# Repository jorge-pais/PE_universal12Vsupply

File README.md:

# Power Electronics - Final Project

This project is a simple and efficient universal 12V switch mode power supply circuit, designed and built for the final project of the Power Electronics Course at KU Leuven - Group T. It is designed around Texas Instruments' LM5175 buck-boost controller IC in order to provide currents up to 2A with an input voltage ranging from 4V to 24V.

## Circuit and PCB

Both the schematic capture and PCB design were done utilizing KiCad 7. These project files can be found the `universal12Vsupply` folder.

It is possible to preview the project online without KiCad through [KiCanvas](https://kicanvas.org/?github=https%3A%2F%2Fgithub.com%2Fjorge-pais%2FPE_universal12Vsupply%2Ftree%2Fmain%2Funiversal12Vsupply).

#### Front View

#### Back View

## Credits

This project was the collaborative effort of the following team members:

- Jorge Pais
- Ranlin Huang
- Samriddha Ray

Their hard work and dedication made this project a success.

## License

This project is licensed under the [Open Source Hardware License 2](LICENSE.md)

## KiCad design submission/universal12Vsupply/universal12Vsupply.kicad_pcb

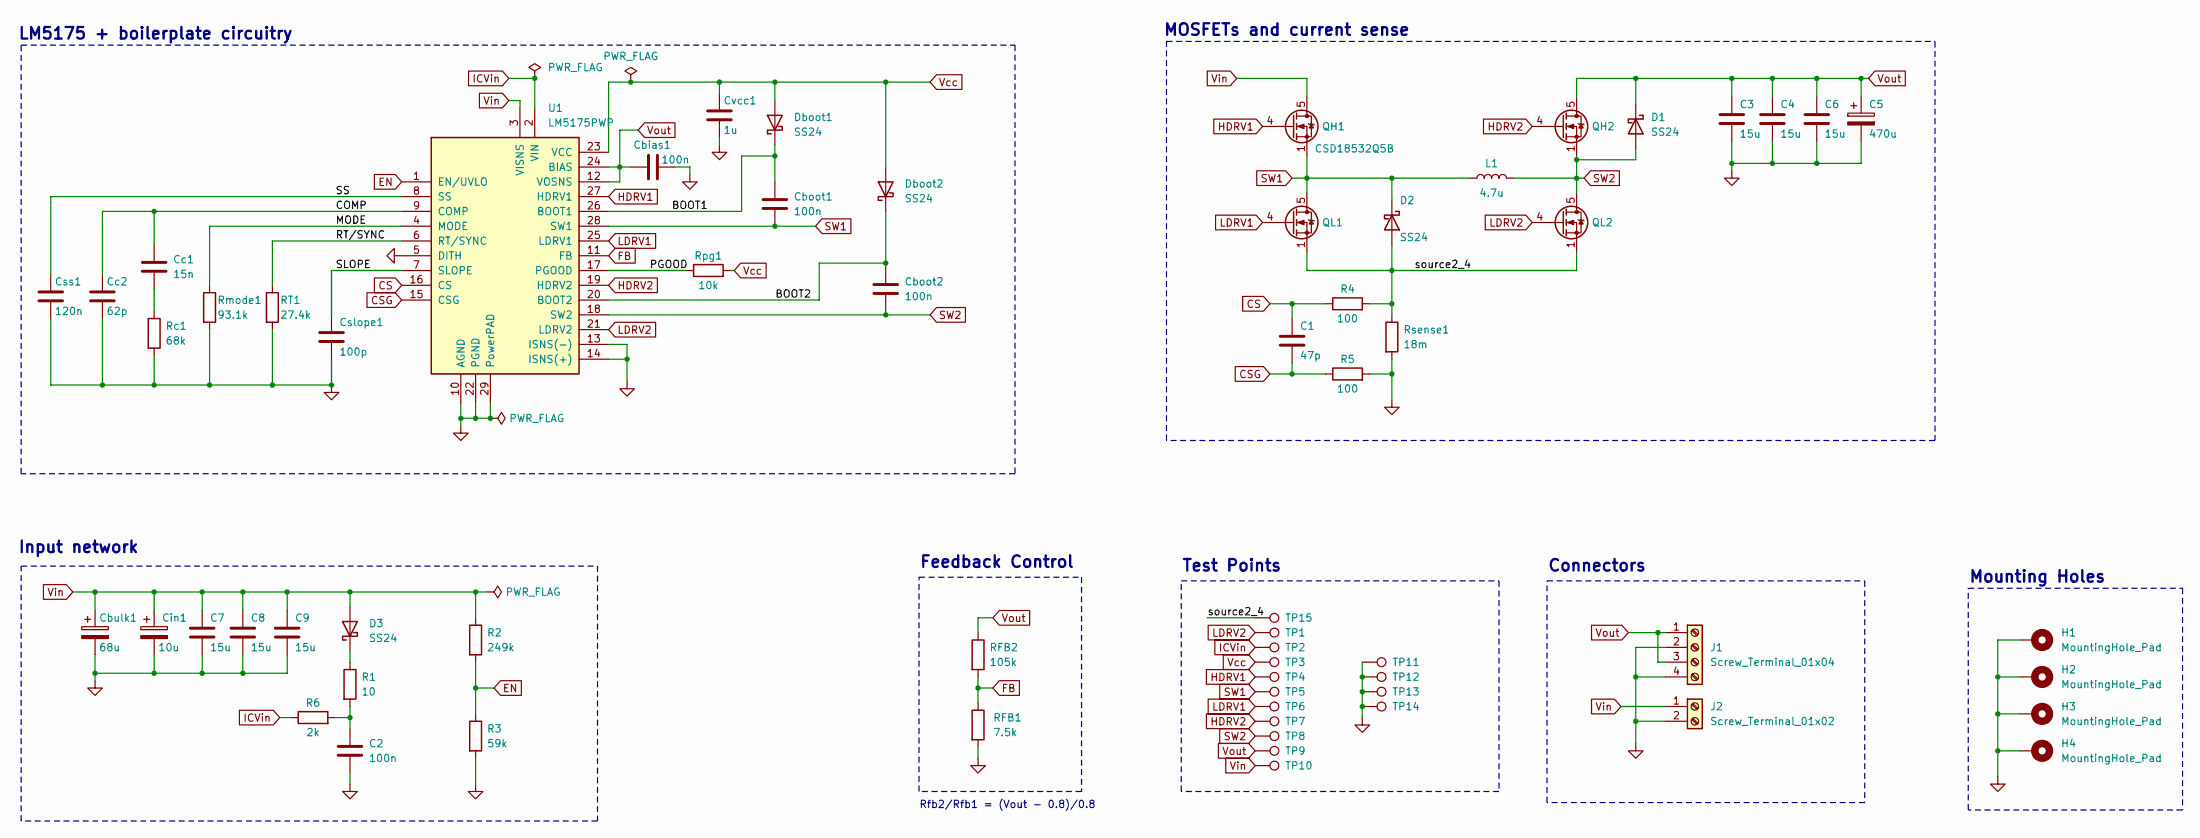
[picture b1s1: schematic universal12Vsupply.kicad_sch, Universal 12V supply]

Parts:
C1: 47p; C_0603_1608Metric_Pad1.08x0.95mm_HandSolder
C2: 100n; C_0805_2012Metric_Pad1.18x1.45mm_HandSolder
C3, C4, C6, C7, C8, C9: 15u; C_1206_3216Metric_Pad1.33x1.80mm_HandSolder
C5: 470u; CP_Elec_10x12.6
Cbias1: 100n; C_0805_2012Metric_Pad1.18x1.45mm_HandSolder
Cboot1, Cboot2: 100n; C_0805_2012Metric_Pad1.18x1.45mm_HandSolder
Cbulk1: 68u; CP_Elec_10x10.5
Cc1: 15n; C_0603_1608Metric_Pad1.08x0.95mm_HandSolder
Cc2: 62p; C_0603_1608Metric_Pad1.08x0.95mm_HandSolder
Cin1: 10u; CP_Elec_5x5.4
Cslope1: 100p; C_0603_1608Metric_Pad1.08x0.95mm_HandSolder
Css1: 120n; C_0603_1608Metric_Pad1.08x0.95mm_HandSolder
Cvcc1: 1u; C_0603_1608Metric_Pad1.08x0.95mm_HandSolder
D1, D2, D3: SS24; D_SMB_Handsoldering
Dboot1, Dboot2: SS24; D_SMB_Handsoldering
H1, H2, H3, H4: MountingHole_Pad; MountingHole_3.2mm_M3_Pad_Via
J1: Screw_Terminal_01x04; TerminalBlock_bornier-4_P5.08mm
J2: Screw_Terminal_01x02; TerminalBlock_bornier-2_P5.08mm
L1: 4.7u; L_Coilcraft_XAL1010-XXX_handsolder
QH1, QH2: CSD18532Q5B; TDSON-8-1
QL1, QL2: CSD18532Q5B; TDSON-8-1
R1: 10; R_0603_1608Metric_Pad0.98x0.95mm_HandSolder
R2: 249k; R_0603_1608Metric_Pad0.98x0.95mm_HandSolder
R3: 59k; R_0603_1608Metric_Pad0.98x0.95mm_HandSolder
R4, R5: 100; R_0603_1608Metric_Pad0.98x0.95mm_HandSolder
R6: 2k; R_0603_1608Metric_Pad0.98x0.95mm_HandSolder
RFB1: 7.5k; R_0603_1608Metric_Pad0.98x0.95mm_HandSolder
RFB2: 105k; R_0603_1608Metric_Pad0.98x0.95mm_HandSolder
RT1: 27.4k; R_0603_1608Metric_Pad0.98x0.95mm_HandSolder
Rc1: 68k; R_0603_1608Metric_Pad0.98x0.95mm_HandSolder
Rmode1: 93.1k; R_0603_1608Metric_Pad0.98x0.95mm_HandSolder
Rpg1: 10k; R_0603_1608Metric_Pad0.98x0.95mm_HandSolder
Rsense1: 18m; R_2512_6332Metric_Pad1.40x3.35mm_HandSolder
TP1: LDRV2; TestPoint_THTPad_2.5x2.5mm_Drill1.2mm
TP2: ICVin; TestPoint_THTPad_2.5x2.5mm_Drill1.2mm
TP3: Vcc; TestPoint_THTPad_2.5x2.5mm_Drill1.2mm
TP4: HDRV1; TestPoint_THTPad_2.5x2.5mm_Drill1.2mm
TP5: SW1; TestPoint_THTPad_2.5x2.5mm_Drill1.2mm
TP6: LDRV1; TestPoint_THTPad_2.5x2.5mm_Drill1.2mm
TP7: HDRV2; TestPoint_THTPad_2.5x2.5mm_Drill1.2mm
TP8: SW2; TestPoint_THTPad_2.5x2.5mm_Drill1.2mm
TP9: Vout; TestPoint_THTPad_2.5x2.5mm_Drill1.2mm
TP10: Vin; TestPoint_THTPad_2.5x2.5mm_Drill1.2mm
TP11, TP12, TP13, TP14: gnd; TestPoint_THTPad_2.5x2.5mm_Drill1.2mm
TP15: source2_4; TestPoint_THTPad_2.5x2.5mm_Drill1.2mm
U1: LM5175PWP; HTSSOP-28-1EP_4.4x9.7mm_P0.65mm_EP3.4x9.5mm_ThermalVias

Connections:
/BOOT1: Cboot1.1, Dboot1.1 (K), U1.26 (BOOT1)
/BOOT2: Cboot2.1, Dboot2.1 (K), U1.20 (BOOT2)
/COMP: Cc1.1, Cc2.1, U1.9 (COMP)
/MODE: Rmode1.1, U1.4 (MODE)
/PGOOD: Rpg1.1, U1.17 (PGOOD)
/RT/SYNC: RT1.1, U1.6 (RT/SYNC)
/SLOPE: Cslope1.1, U1.7 (SLOPE)
/SS: Css1.1, U1.8 (SS)
/source2_4: D2.2 (A), QL1.1 (S), QL1.2 (S), QL1.3 (S), QL2.1 (S), QL2.2 (S), QL2.3 (S), R4.2, Rsense1.1, TP15.1
CS: C1.1, R4.1, U1.16 (CS)
CSG: C1.2, R5.1, U1.15 (CSG)
EN: R2.2, R3.1, U1.1 (EN/UVLO)
FB: RFB1.1, RFB2.2, U1.11 (FB)
GND: C2.2, C3.2, C4.2, C5.2, C6.2, C7.2, C8.2, C9.2, Cbias1.2, Cbulk1.2, Cc2.2, Cin1.2, Cslope1.2, Css1.2, Cvcc1.2, H1.1, H2.1, H3.1, H4.1, J1.2, J1.4, J2.2, R3.2, R5.2, RFB1.2, RT1.2, Rc1.2, Rmode1.2, Rsense1.2, TP11.1, TP12.1, TP13.1, TP14.1, U1.5 (DITH), U1.10 (AGND), U1.13 (ISNS(-)), U1.14 (ISNS(+)), U1.22 (PGND), U1.29 (PowerPAD)
HDRV1: QH1.4 (G), TP4.1, U1.27 (HDRV1)
HDRV2: QH2.4 (G), TP7.1, U1.19 (HDRV2)
ICVin: R6.1, TP2.1, U1.2 (VIN)
LDRV1: QL1.4 (G), TP6.1, U1.25 (LDRV1)
LDRV2: QL2.4 (G), TP1.1, U1.21 (LDRV2)
unnamed: C2.1, R1.2, R6.2
unnamed: Cc1.2, Rc1.1
unnamed: D3.1 (K), R1.1
SW1: Cboot1.2, D2.1 (K), L1.1, QH1.1 (S), QH1.2 (S), QH1.3 (S), QL1.5 (D), TP5.1, U1.28 (SW1)
SW2: Cboot2.2, D1.2 (A), L1.2, QH2.1 (S), QH2.2 (S), QH2.3 (S), QL2.5 (D), TP8.1, U1.18 (SW2)
Vcc: Cvcc1.1, Dboot1.2 (A), Dboot2.2 (A), Rpg1.2, TP3.1, U1.23 (VCC)
Vin: C7.1, C8.1, C9.1, Cbulk1.1, Cin1.1, D3.2 (A), J2.1, QH1.5 (D), R2.1, TP10.1, U1.3 (VISNS)
Vout: C3.1, C4.1, C5.1, C6.1, Cbias1.1, D1.1 (K), J1.1, J1.3, QH2.5 (D), RFB2.1, TP9.1, U1.12 (VOSNS), U1.24 (BIAS)

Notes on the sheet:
Feedback Control
MOSFETs and current sense
Rfb2/Rfb1 = (Vout - 0.8)/0.8
Mounting Holes
Input network
Connectors
LM5175 + boilerplate circuitry
Test Points

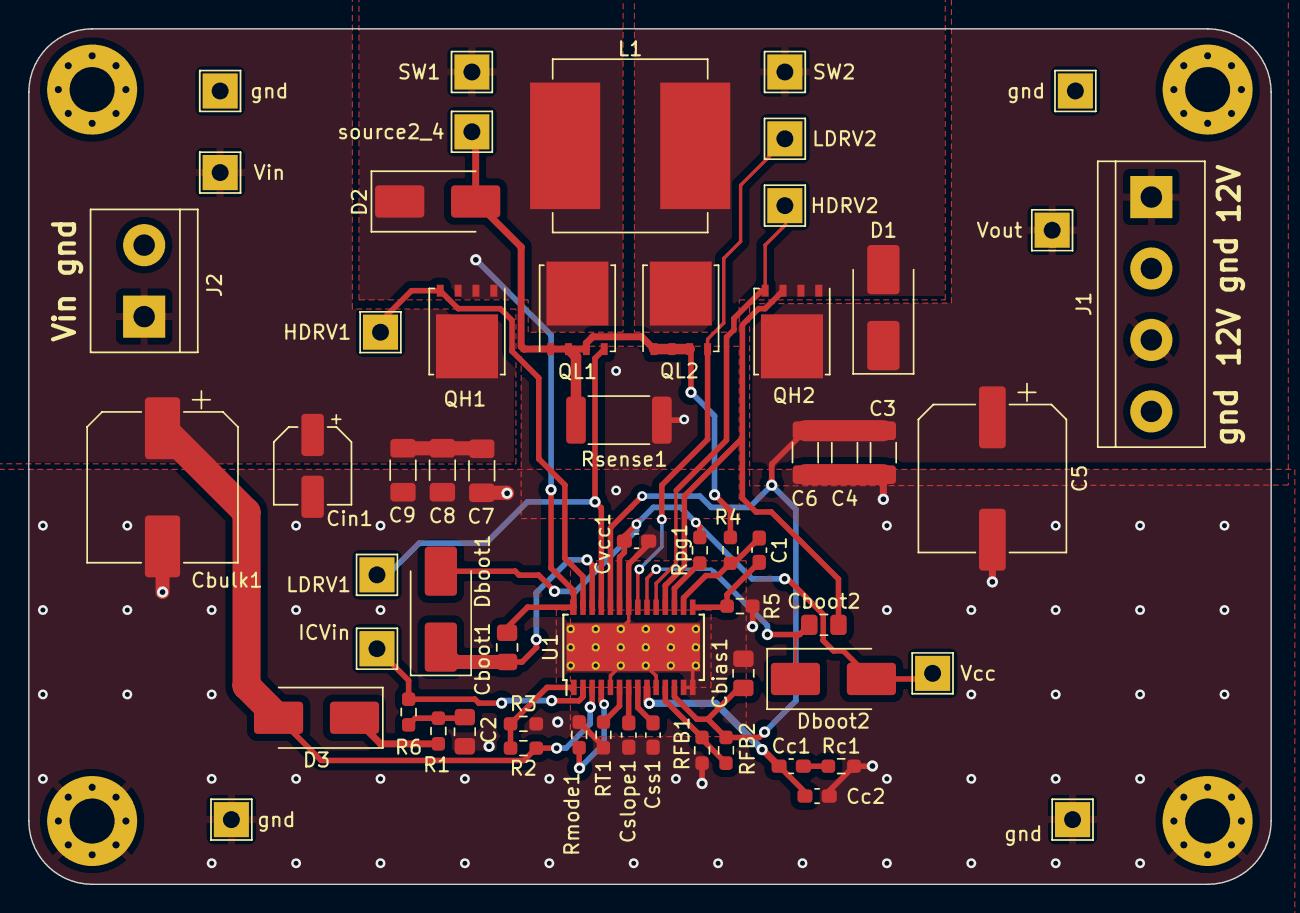
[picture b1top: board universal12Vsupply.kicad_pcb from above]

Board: 2 copper layers, 88.3 x 60.8 mm, 64 parts (0 on the bottom side), 27 nets.

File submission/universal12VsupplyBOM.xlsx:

Reference | Value | Footprint | Datasheet | Farnell | Qty | Order Code
C1 | 47p | Capacitor_SMD:C_0603_1608Metric_Pad1.08x0.95mm_HandSolder | ~ | https://be.farnell.com/en-BE/kemet/c0603c470f1gactu/cap-47pf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 | 1 | 2820807
C2 | 100n | Capacitor_SMD:C_0805_2012Metric_Pad1.18x1.45mm_HandSolder | ~ | https://be.farnell.com/en-BE/kemet/c0805x104j5rac3316/cap-0-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 | 1 | 2666904
C3, C4, C6, C7, C8, C9 | 15u | Capacitor_SMD:C_1206_3216Metric_Pad1.33x1.80mm_HandSolder | ~ | https://be.farnell.com/en-BE/avx/tpsa156k006r0700/cap-15-f-6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 | 6 | 1658485
C5 | 470u | Capacitor_SMD:CP_Elec_10x12.6 | ~ | https://be.farnell.com/en-BE/panasonic/25svpk470m/cap-470-f-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 | 1 | 2759084
Cbias1 | 100n | Capacitor_SMD:C_0805_2012Metric_Pad1.18x1.45mm_HandSolder | ~ | https://be.farnell.com/en-BE/kemet/c0805x104j5rac3316/cap-0-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 | 1 | 2666904
Cboot1, Cboot2 | 100n | Capacitor_SMD:C_0805_2012Metric_Pad1.18x1.45mm_HandSolder | ~ | https://be.farnell.com/en-BE/kemet/c0805x104j5rac3316/cap-0-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 | 2 | 2666904
Cbulk1 | 68u | Capacitor_SMD:CP_Elec_10x10.5 | ~ | https://be.farnell.com/en-BE/panasonic/eehzt1j680p/cap-68uf-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 | 1 | 3584428
Cc1 | 15n | Capacitor_SMD:C_0603_1608Metric_Pad1.08x0.95mm_HandSolder | ~ | https://be.farnell.com/en-BE/multicomp/mc0603b153j500ct/cap-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 | 1 | 2320805
Cc2 | 62p | Capacitor_SMD:C_0603_1608Metric_Pad1.08x0.95mm_HandSolder | ~ | https://be.farnell.com/en-BE/kemet/c0603c620j5gactu/cap-62pf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 | 1 | 1865482
Cin1 | 10u | Capacitor_SMD:CP_Elec_5x5.4 | ~ | https://be.farnell.com/en-BE/kemet/exv106m035a9daa/cap-10-f-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 | 1 | 2069187
Cslope1 | 100p | Capacitor_SMD:C_0603_1608Metric_Pad1.08x0.95mm_HandSolder | ~ | https://be.farnell.com/en-BE/kemet/c0603x101f5gacauto/cap-10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 | 1 | 2904893
Cvcc1 | 1u | Capacitor |  | https://be.farnell.com/en-BE/kemet/c0805c105j8ractu/cap-1-f-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 | 1 | 2773210
Css1 | 120n | Capacitor_SMD:C_0603_1608Metric_Pad1.08x0.95mm_HandSolder | ~ | https://be.farnell.com/en-BE/kemet/c0603c124k8ractu/cap-0-12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 | 1 | 2821085
D1-D3 | SS24 | Diode_SMD:D_SMB_Handsoldering | ~ | https://be.farnell.com/en-BE/multicomp/ss24/schottky-rectifi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 | 3 | 2675138
Dboot1, Dboot2 | SS24 | Diode_SMD:D_SMB_Handsoldering | ~ | https://be.farnell.com/en-BE/multicomp/ss24/schottky-rectifi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 | 2 | 2675138
L1 | 4.7u | Inductor_SMD:L_Coilcraft_XAL1010-XXX | ~ | https://be.farnell.com/en-BE/coilcraft/xal1010-472med/induct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 | 1 | 2289017
QH1, QH2 | CSD18532Q5B | Package_TO_SOT_SMD:TDSON-8-1 | http://www.ti.com/lit/gpn/csd18532q5b | https://be.farnell.com/en-BE/texas-instruments/csd18532q5b/m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 | 2 | 3009663
QL1, QL2 | CSD18532Q5B | Package_TO_SOT_SMD:TDSON-8-1 | http://www.ti.com/lit/gpn/csd18532q5b | https://be.farnell.com/en-BE/texas-instruments/csd18532q5b/m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 | 2 | 3009663
R1 | 10R | Resistor_SMD:R_0603_1608Metric_Pad0.98x0.95mm_HandSolder | ~ | https://be.farnell.com/en-BE/rohm/ktr03ezpf10r0/res-10r-1-0-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 | 1 | 2919225
R2 | 249k | Resistor_SMD:R_0603_1608Metric_Pad0.98x0.95mm_HandSolder | ~ | https://be.farnell.com/en-BE/panasonic/erjpa3f2493v/res-249k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 | 1 | 2561907
R3 | 59k | Resistor_SMD:R_0603_1608Metric_Pad0.98x0.95mm_HandSolder | ~ | https://be.farnell.com/en-BE/panasonic/erjpa3f5902v/res-59k-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 | 1 | 2562106
R4, R5 | 100R | Resistor_SMD:R_0603_1608Metric_Pad0.98x0.95mm_HandSolder | ~ | https://be.farnell.com/en-BE/vishay/rca0603100rfkea/res-100r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 | 2 | 2616583
R6 | 2k | Resistor_SMD:R_0603_1608Metric_Pad0.98x0.95mm_HandSolder | ~ | https://be.farnell.com/en-BE/panasonic/era3arw202v/res-2k-0-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 | 1 | 2797306
Rc1 | 68k | Resistor_SMD:R_0603_1608Metric_Pad0.98x0.95mm_HandSolder | ~ | https://be.farnell.com/en-BE/te-connectivity/crgcq0603f68k/r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 | 1 | 2861483
RFB1 | 7.5k | Resistor_SMD:R_0603_1608Metric_Pad0.98x0.95mm_HandSolder | ~ | https://be.farnell.com/en-BE/multicomp-pro/mcsr06x7501ftl/re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 | 1 | 2074303
RFB2 | 105k | Resistor_SMD:R_0603_1608Metric_Pad0.98x0.95mm_HandSolder | ~ | https://be.farnell.com/en-BE/panasonic/erjpa3f1053v/res-105k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 | 1 | 2561729
Rmode1 | 93.1k | Resistor_SMD:R_0603_1608Metric_Pad0.98x0.95mm_HandSolder | ~ | https://be.farnell.com/en-BE/panasonic/erjpa3f9312v/res-93k1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 | 1 | 2562207
Rpg1 | 10k | Resistor_SMD:R_0603_1608Metric_Pad0.98x0.95mm_HandSolder | ~ | https://be.farnell.com/en-BE/vishay/rca060310k0fkea/res-10k-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 | 1 | 2616584
Rsense1 | 18m | Resistor_SMD:R_2512_6332Metric_Pad1.40x3.35mm_HandSolder | ~ | https://be.farnell.com/en-BE/multicomp/mchvr12ftft1805/res-t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 | 1 | 2826912
RT1 | 27.4k | Resistor_SMD:R_0603_1608Metric_Pad0.98x0.95mm_HandSolder | ~ | https://be.farnell.com/en-BE/panasonic/erjpa3f2742v/res-27k4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 | 1 | 2561929
U1 | LM5175PWP | Package_SO:HTSSOP-28-1EP_4.4x9.7mm_P0.65mm_EP3.4x9.5mm_ThermalVias | http://www.ti.com/lit/ds/symlink/lm5175.pdf | https://be.farnell.com/en-BE/texas-instruments/lm5175pwpt/dc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 | 1 | 3008670

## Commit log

2023-11-04 added PCB constraints based on JLC PCB restraints
2023-11-04 started PCB layout
2023-11-04 'finalised' layout without DRC errors
2023-11-11 design clean up
2023-11-11 added test points properly, DRC and ERC is fine
2023-11-11 added via stiching
2023-11-11 increased via stiching spacing
2023-11-15 finished PCB
2023-11-17 circuit changes, simulation, final (final) PCB layout and GERBER+drill files
2023-11-17 repository organization
2023-12-21 added design report i think
